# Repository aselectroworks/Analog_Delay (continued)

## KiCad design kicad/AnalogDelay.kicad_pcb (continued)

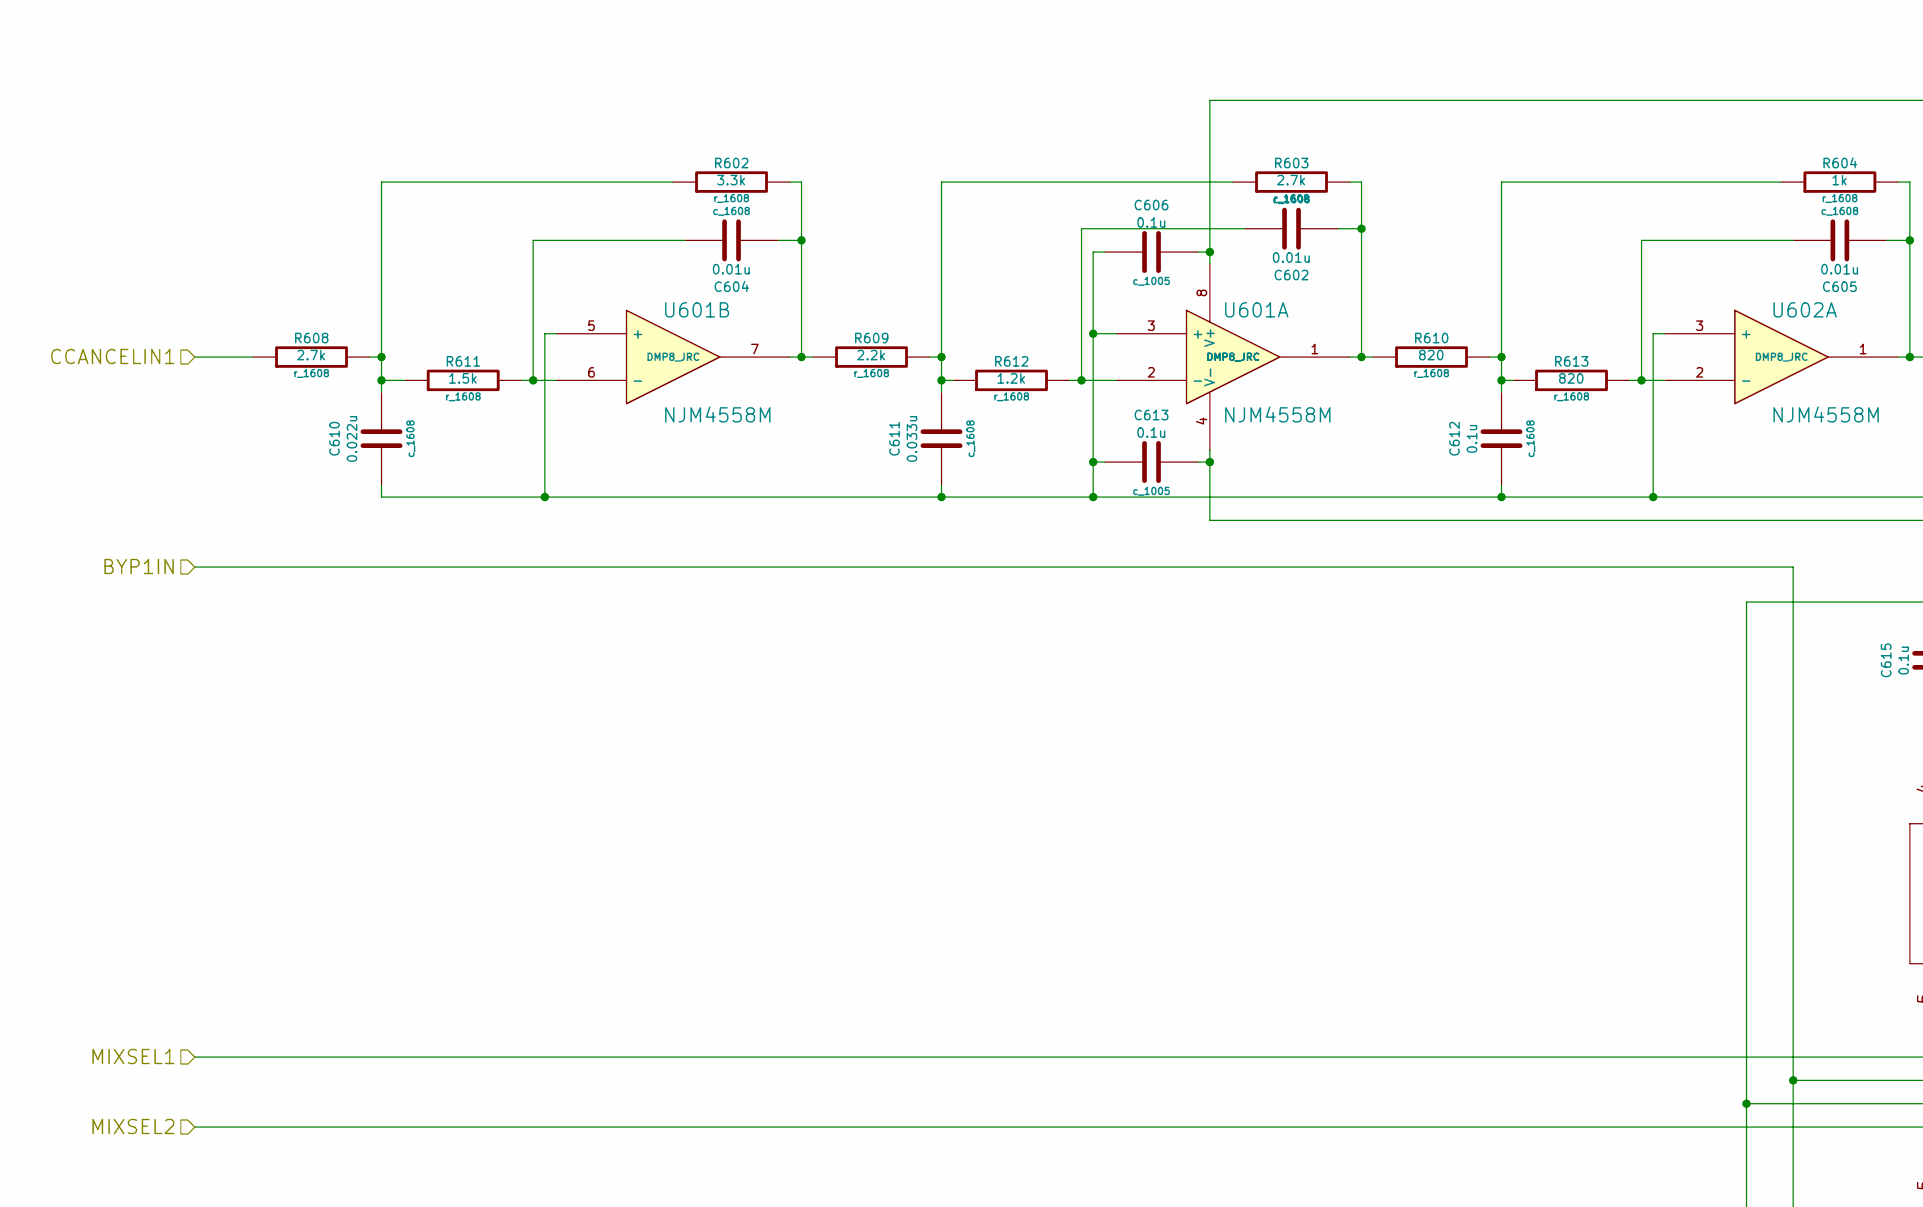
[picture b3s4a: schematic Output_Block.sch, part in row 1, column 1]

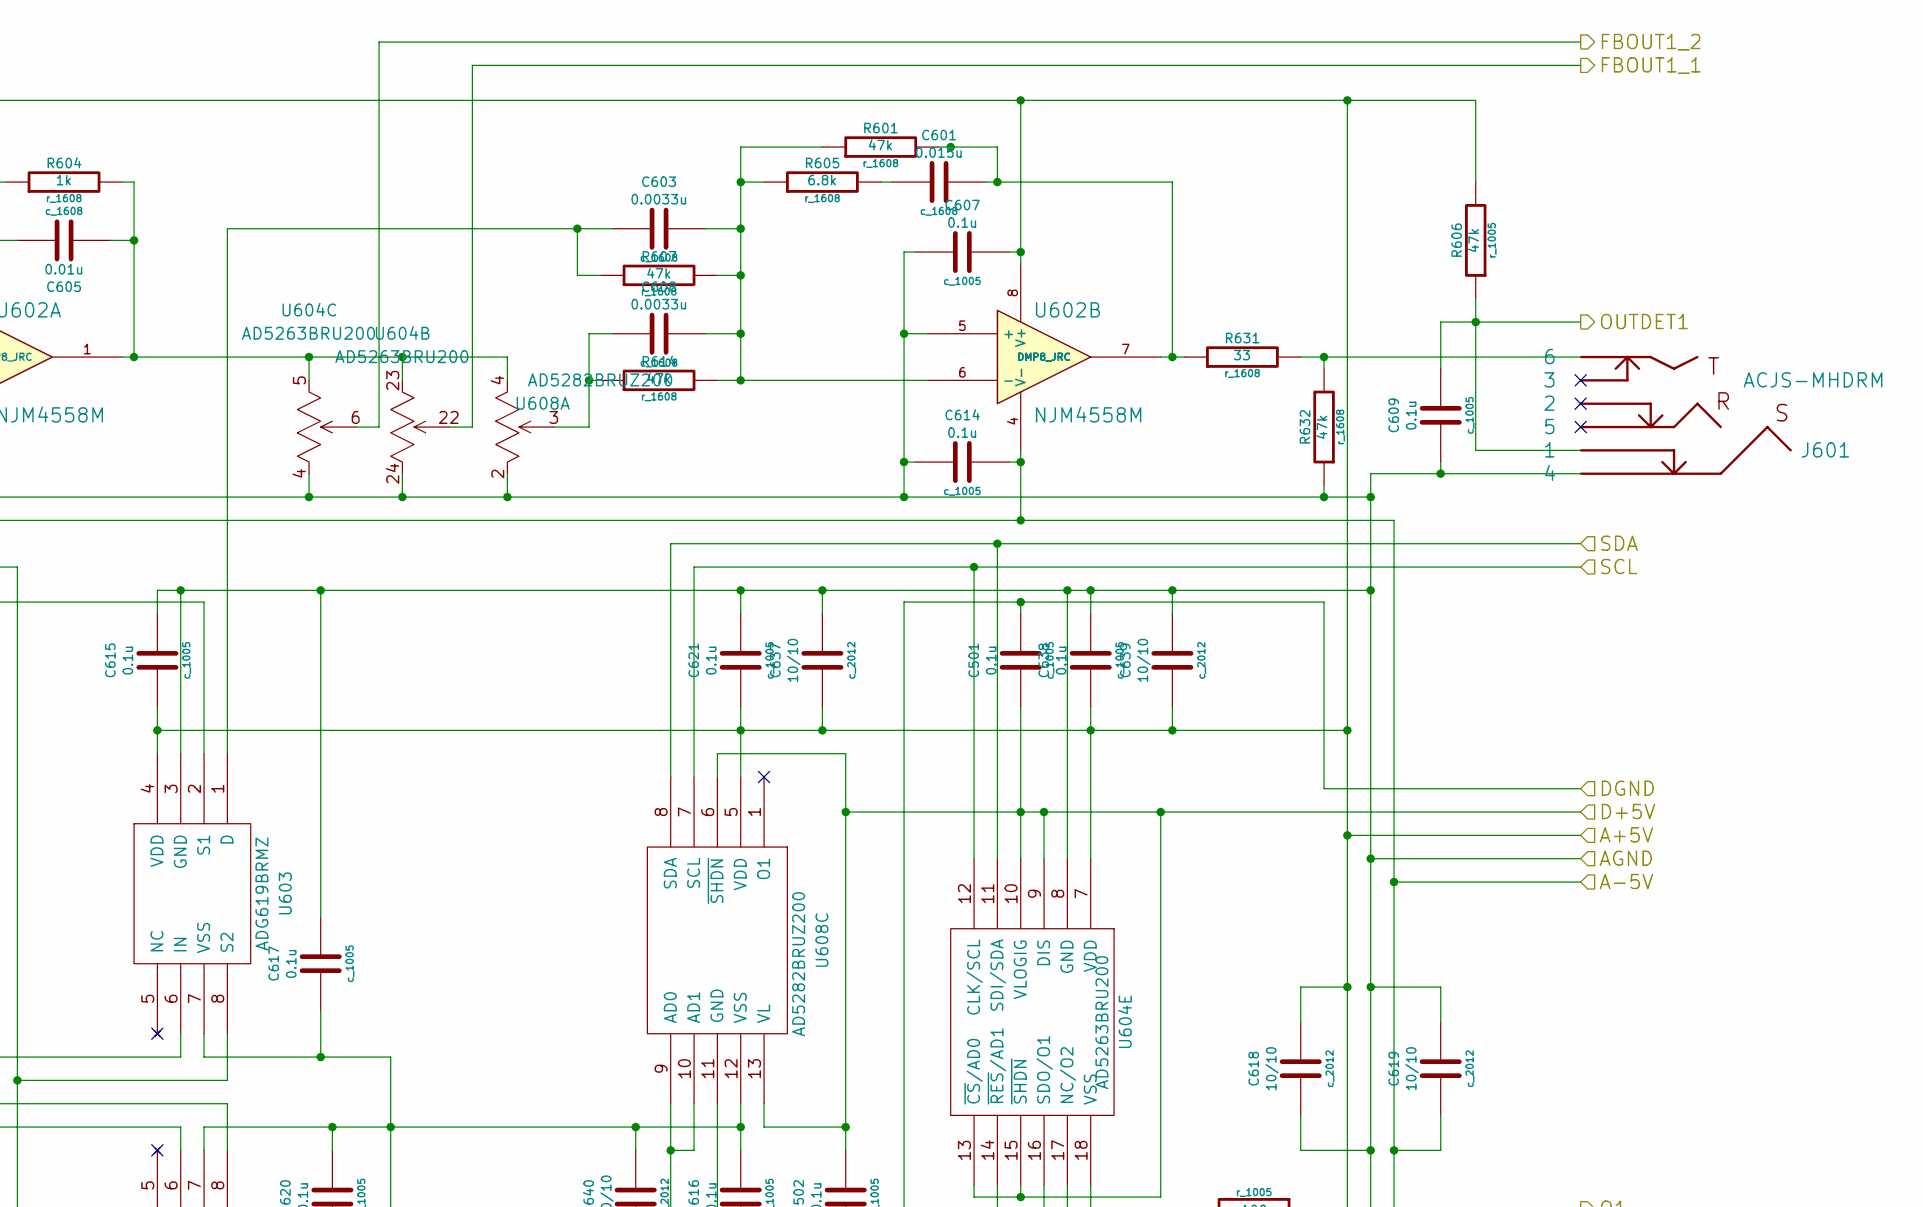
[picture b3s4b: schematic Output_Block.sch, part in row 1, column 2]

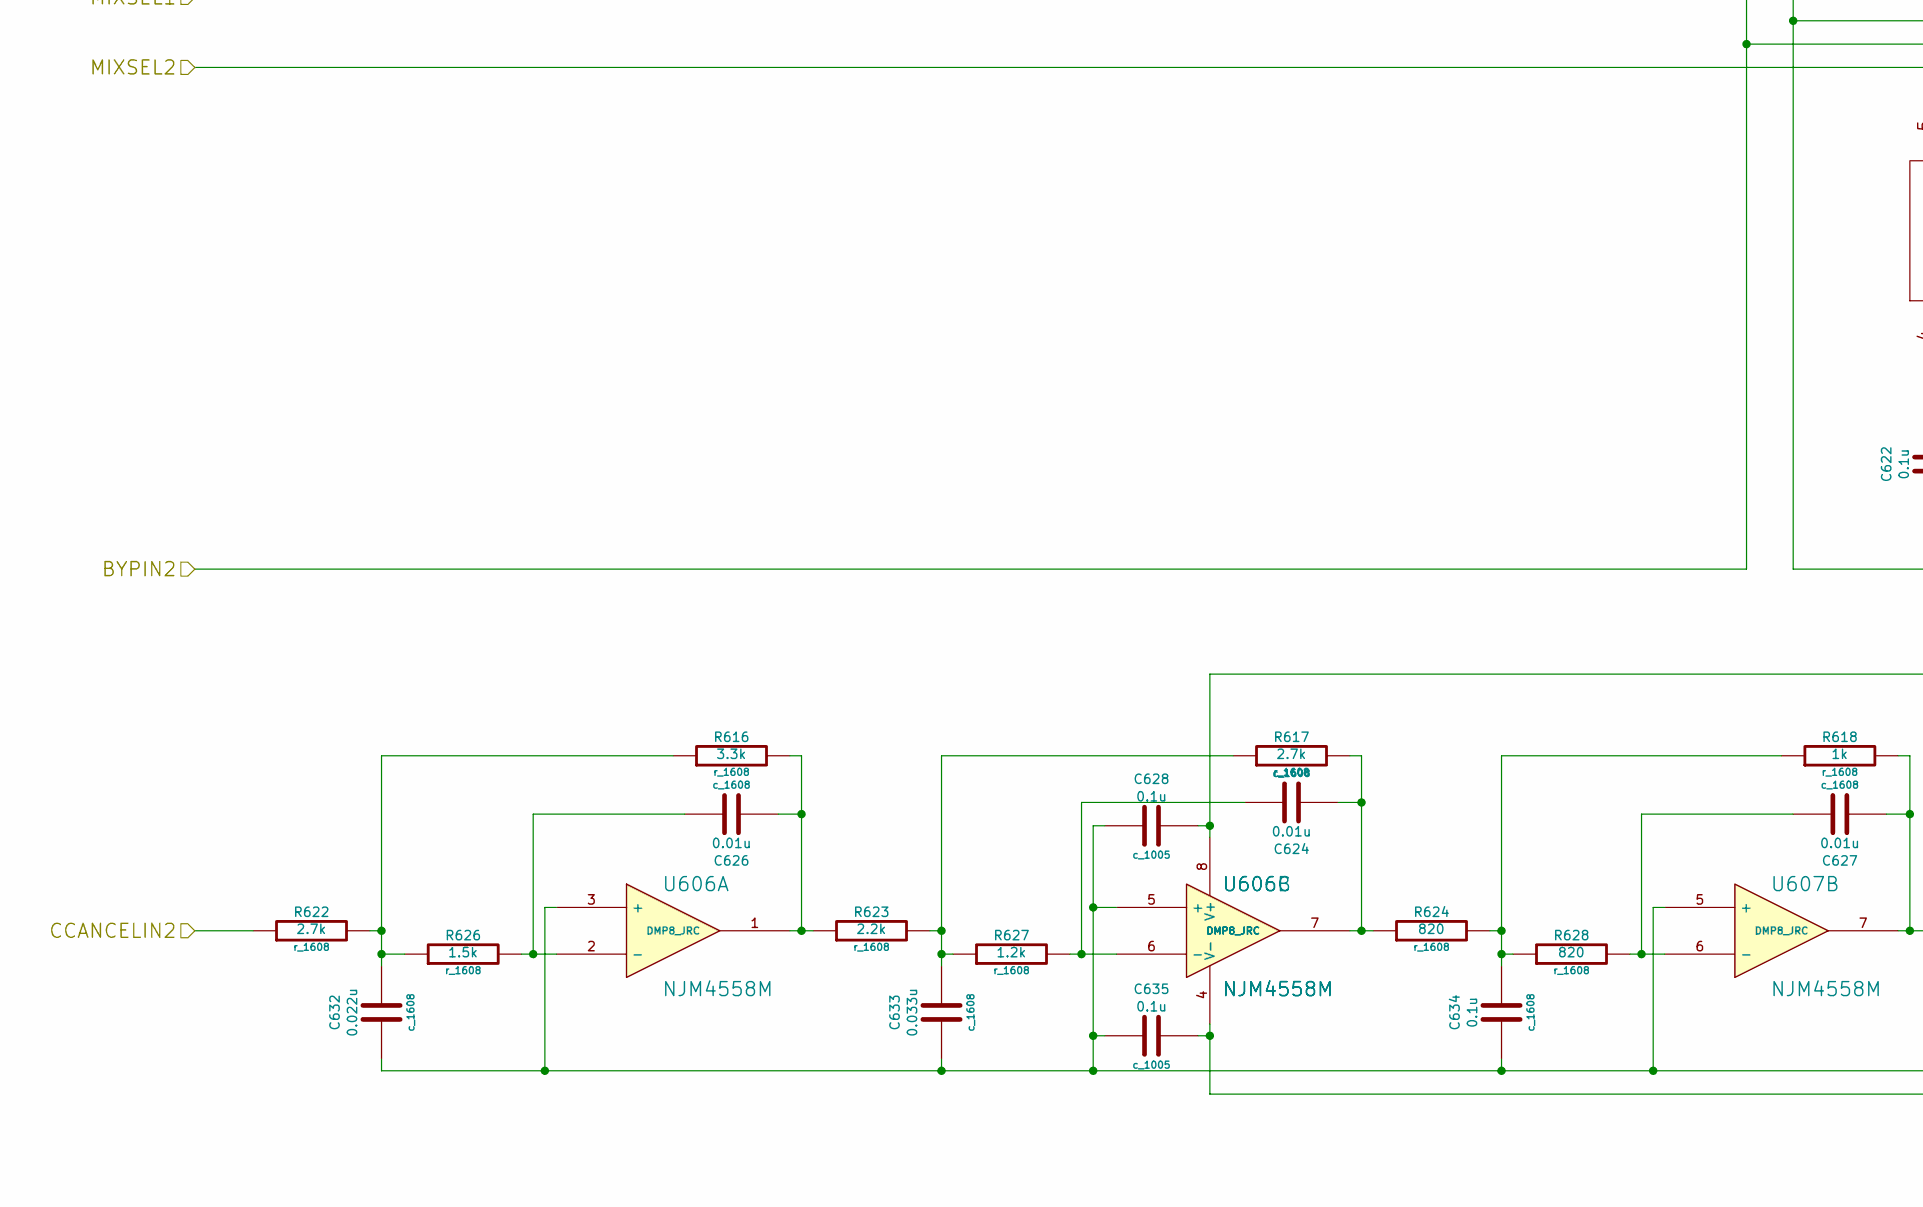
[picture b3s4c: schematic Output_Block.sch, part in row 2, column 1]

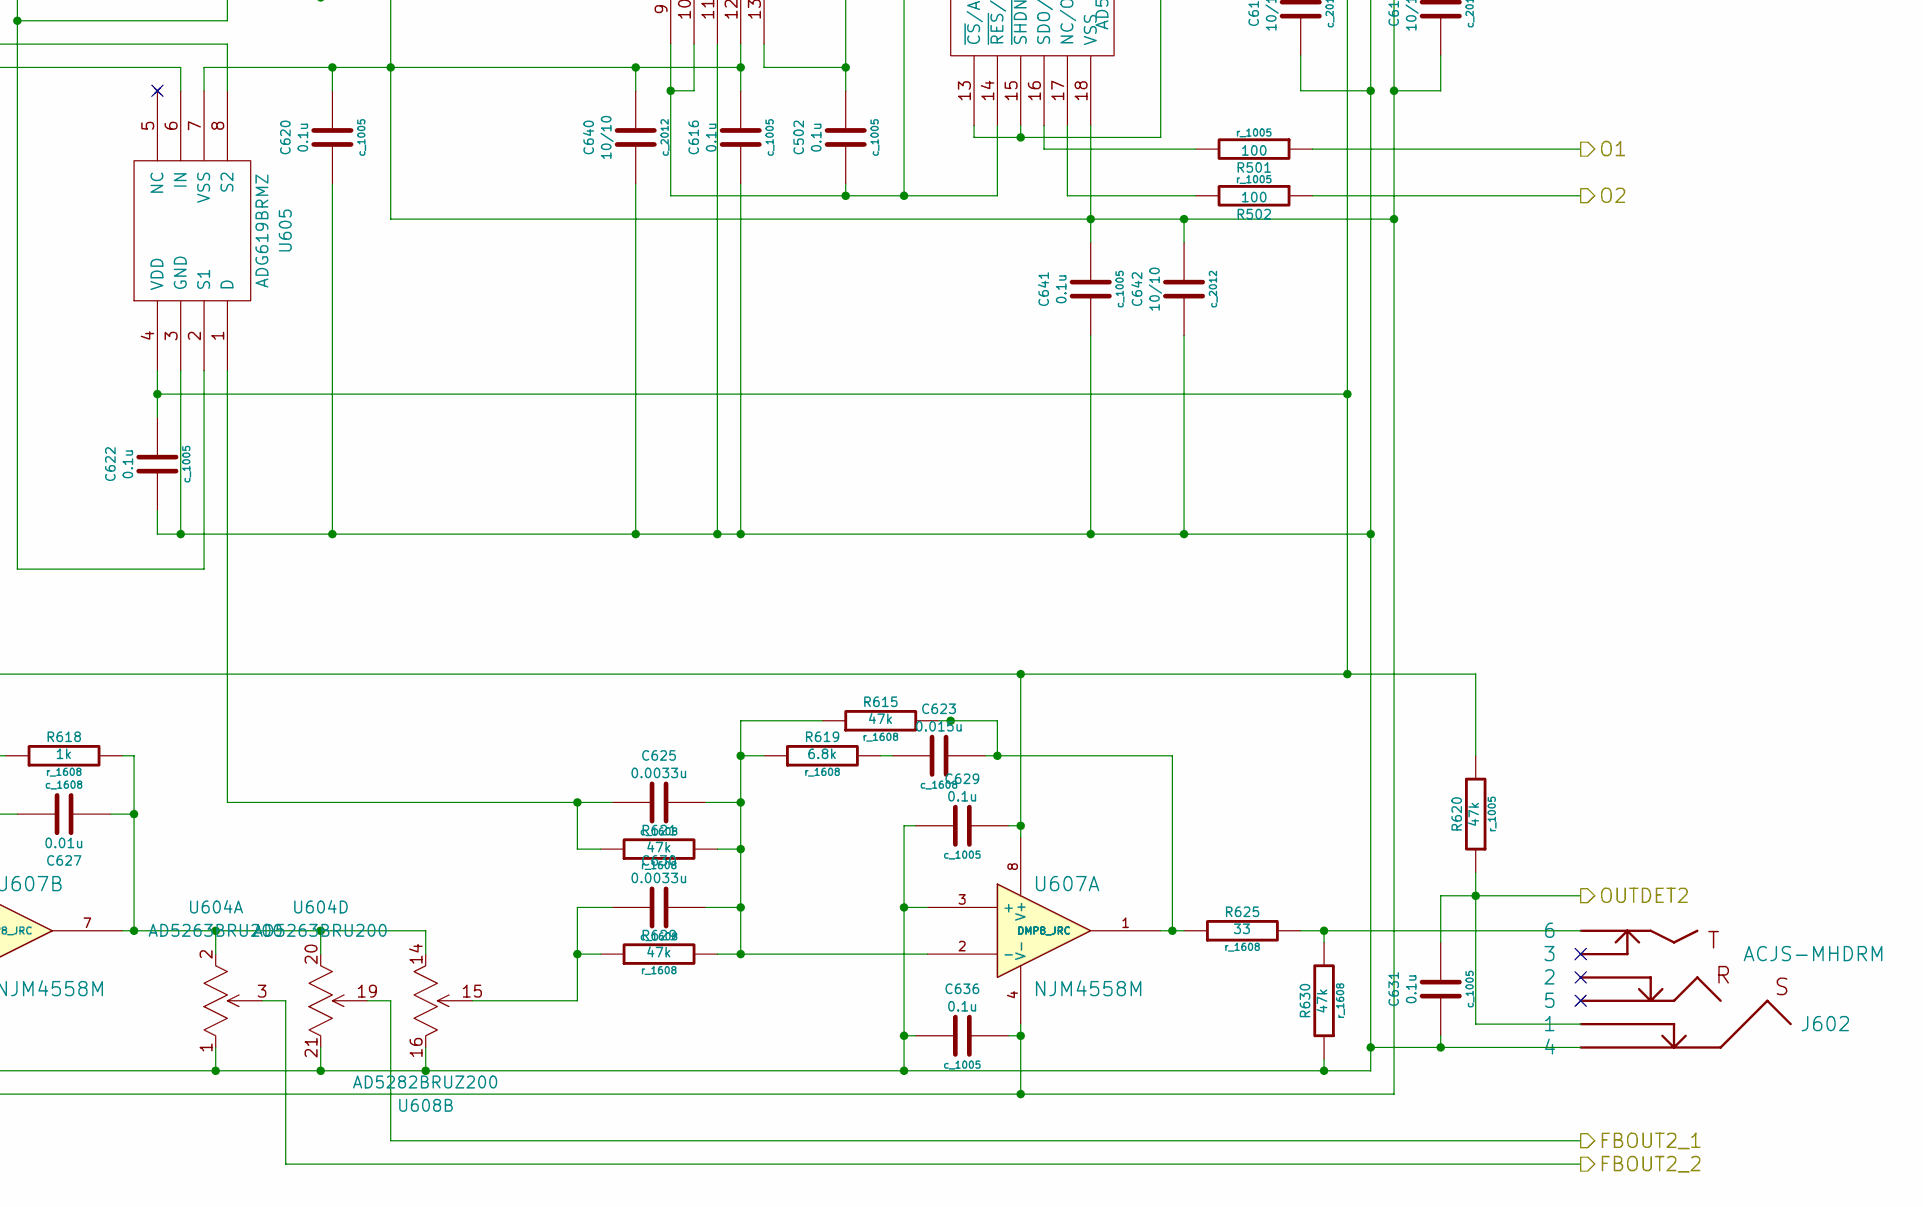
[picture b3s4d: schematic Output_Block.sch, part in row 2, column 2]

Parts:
C501, C502, C606, C607, C609, C613, C614, C615, C616, C617, C620, C621, C622, C628, C629, C631, C635, C636, C638, C641: 0.1u; c_1005
C601, C623: 0.015u; c_1608
C602, C604, C605, C624, C626, C627: 0.01u; c_1608
C603, C608, C625, C630: 0.0033u; c_1608
C610, C632: 0.022u; c_1608
C611, C633: 0.033u; c_1608
C612, C634: 0.1u; c_1608
C618, C619, C637, C639, C640, C642: 10/10; c_2012
J601, J602: ACJS-MHDRM
R501, R502: 100; r_1005
R601, R607, R614, R615, R621, R629, R630, R632: 47k; r_1608
R602, R616: 3.3k; r_1608
R603, R608, R617, R622: 2.7k; r_1608
R604, R618: 1k; r_1608
R605, R619: 6.8k; r_1608
R606, R620: 47k; r_1005
R609, R623: 2.2k; r_1608
R610, R613, R624, R628: 820; r_1608
R611, R626: 1.5k; r_1608
R612, R627: 1.2k; r_1608
R625, R631: 33; r_1608
U601, U602, U606, U607: NJM4558M; DMP8_JRC
U603, U605: ADG619BRMZ; RM-8
U604: AD5263BRU200; RU-24
U608: AD5282BRUZ200; RU-16

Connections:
+5VA: C606.2, C607.2, C615.1, C618.2, C621.1, C622.2, C628.2, C629.2, C637.1, C638.1, C639.1, R606.2, R620.2, U601.8 (V+), U602.8 (V+), U603.4 (VDD), U604.7 (VDD), U605.4 (VDD), U606.8 (V+), U607.8 (V+), U608.5 (VDD); also elsewhere on the board
+5VD: C501.1, C502.2, U604.9 (DIS), U604.10 (VLOGIG), U604.13 (~CS~/AD0), U604.15 (~SHDN), U608.6 (~SHDN), U608.13 (VL); also elsewhere on the board
-5VA: C613.2, C614.2, C616.2, C617.1, C619.1, C620.2, C635.2, C636.2, C640.2, C641.2, C642.2, U601.4 (V-), U602.4 (V-), U603.7 (VSS), U604.18 (VSS), U605.7 (VSS), U606.4 (V-), U607.4 (V-), U608.12 (VSS); also elsewhere on the board
/BBD Block/BBDOUT1: R608.1; also elsewhere on the board
/BBD Block/BBDOUT2: R622.1; also elsewhere on the board
/Clock Cancel Filter/Output Block/BYP1IN: U603.8 (S2), U605.2 (S1); also elsewhere on the board
/Clock Cancel Filter/Output Block/BYPIN2: U603.2 (S1), U605.8 (S2); also elsewhere on the board
/Clock Cancel Filter/Output Block/MIXSEL1: R501.1, U603.6 (IN)
/Clock Cancel Filter/Output Block/MIXSEL2: R502.1, U605.6 (IN)
/Clock Cancel Filter/Output Block/OUTDET1: C609.2, J601.1, R606.1; also elsewhere on the board
/Clock Cancel Filter/Output Block/OUTDET2: C631.2, J602.1, R620.1; also elsewhere on the board
/Clock Cancel Filter/Output Block/SCL: U604.12 (CLK/SCL), U608.7 (SCL); also elsewhere on the board
/Clock Cancel Filter/Output Block/SDA: U604.11 (SDI/SDA), U608.8 (SDA); also elsewhere on the board
/Input/Anti Alias Filter Block/FBIN1_1: U604.22 (W2); also elsewhere on the board
/Input/Anti Alias Filter Block/FBIN1_2: U604.6 (W3); also elsewhere on the board
/Input/Anti Alias Filter Block/FBIN2_1: U604.19 (W4); also elsewhere on the board
/Input/Anti Alias Filter Block/FBIN2_2: U604.3 (W1); also elsewhere on the board
AGND: C606.1, C607.1, C609.1, C610.1, C611.1, C612.1, C613.1, C614.1, C615.2, C616.1, C617.2, C618.1, C619.2, C620.1, C621.2, C622.1, C628.1, C629.1, C631.1, C632.1, C633.1, C634.1, C635.1, C636.1, C637.2, C638.2, C639.2, C640.1, C641.1, C642.1, J601.4, J602.4, R630.1, R632.1, U601.3 (+), U601.5 (+), U602.3 (+), U602.5 (+), U603.3 (GND), U604.1 (B1), U604.4 (B3), U604.8 (GND), U604.21 (B4), U604.24 (B2), U605.3 (GND), U606.3 (+), U606.5 (+), U607.3 (+), U607.5 (+), U608.2 (A1), U608.11 (GND), U608.16 (A1); also elsewhere on the board
DGND: C501.2, C502.1, U604.14 (~RES~/AD1), U608.9 (AD0), U608.10 (AD1); also elsewhere on the board
unnamed: J602.6, R625.2, R630.2
unnamed: C630.1, R629.1, U608.15 (W2)
unnamed: J601.6, R631.2, R632.2
unnamed: C612.2, R604.1, R610.2, R613.1
unnamed: C602.1, R603.2, R610.1, U601.1
unnamed: C602.2, R612.2, U601.2 (-)
unnamed: C608.1, R614.1, U608.3 (W2)
unnamed: C611.2, R603.1, R609.2, R612.1
unnamed: C605.2, R613.2, U602.2 (-)
unnamed: C601.1, R605.2
unnamed: C604.2, R611.2, U601.6 (-)
unnamed: C604.1, R602.2, R609.1, U601.7
unnamed: C610.2, R602.1, R608.2, R611.1
unnamed: C601.2, R601.2, R631.1, U602.7
unnamed: C627.2, R628.2, U607.6 (-)
unnamed: C634.2, R618.1, R624.2, R628.1
unnamed: C624.1, R617.2, R624.1, U606.7
unnamed: C625.1, R621.1, U605.1 (D)
unnamed: C624.2, R627.2, U606.6 (-)
unnamed: C627.1, R618.2, U604.2 (A1), U604.20 (A4), U607.7, U608.14 (B1)
unnamed: C623.2, R615.2, R625.1, U607.1
unnamed: C623.1, R619.2
unnamed: C625.2, C630.2, R615.1, R619.1, R621.2, R629.2, U607.2 (-)
unnamed: C603.1, R607.1, U603.1 (D)
unnamed: C603.2, C608.2, R601.1, R605.1, R607.2, R614.2, U602.6 (-)
unnamed: C633.2, R617.1, R623.2, R627.1
unnamed: C626.1, R616.2, R623.1, U606.1
unnamed: C626.2, R626.2, U606.2 (-)
unnamed: C632.2, R616.1, R622.2, R626.1
unnamed: R501.2, U604.16 (SDO/O1)
unnamed: R502.2, U604.17 (NC/O2)
unnamed: C605.1, R604.2, U602.1, U604.5 (A3), U604.23 (A2), U608.4 (B1)

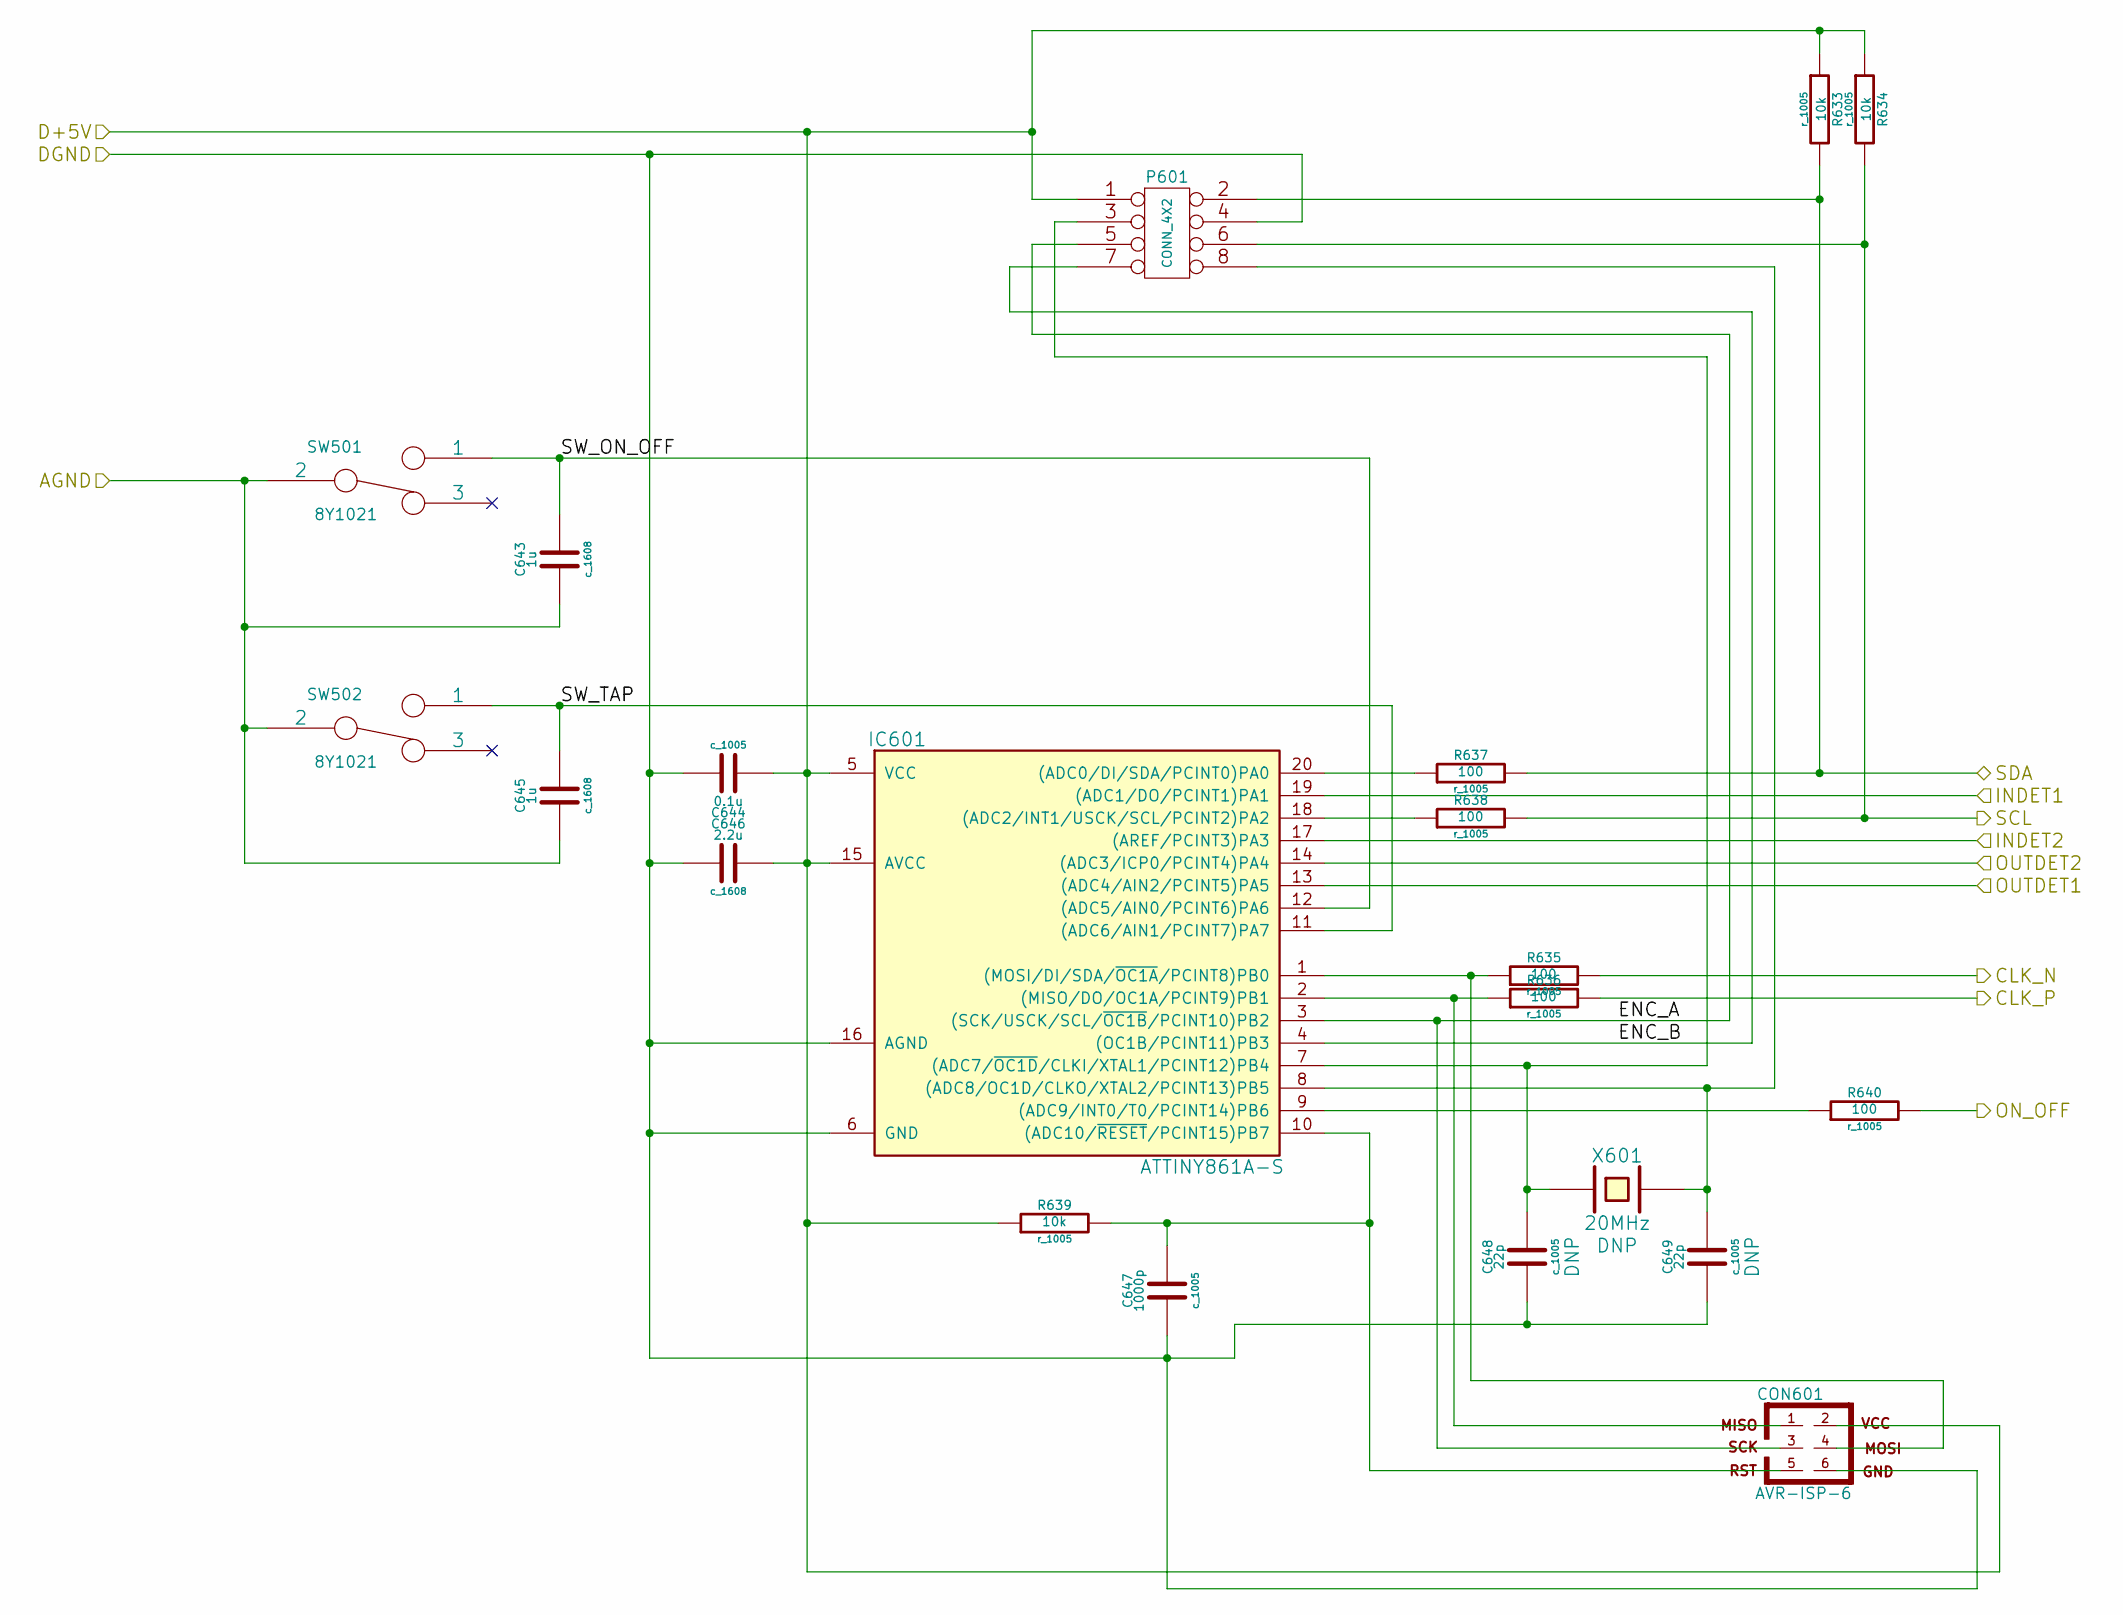
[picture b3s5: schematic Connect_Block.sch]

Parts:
C643, C645: 1u; c_1608
C644: 0.1u; c_1005
C646: 2.2u; c_1608
C647: 1000p; c_1005
C648, C649: 22p; c_1005
CON601: AVR-ISP-6
IC601: ATTINY861A-S; SO20
P601: CONN_4X2
R633, R634, R639: 10k; r_1005
R635, R636, R637, R638, R640: 100; r_1005
SW501, SW502: 8Y1021; 8Y10
X601: 20MHz

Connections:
+5VD: C644.1, C646.2, CON601.2, IC601.5 (VCC), IC601.15 (AVCC), P601.1, R633.1, R634.1, R639.1; also elsewhere on the board
/BBD Block/CLK_N: R635.2; also elsewhere on the board
/BBD Block/CLK_P: R636.2; also elsewhere on the board
/Clock Cancel Filter/Output Block/OUTDET1: IC601.13 ((ADC4/AIN2/PCINT5)PA5); also elsewhere on the board
/Clock Cancel Filter/Output Block/OUTDET2: IC601.14 ((ADC3/ICP0/PCINT4)PA4); also elsewhere on the board
/Clock Cancel Filter/Output Block/SCL: P601.6, R634.2, R638.2; also elsewhere on the board
/Clock Cancel Filter/Output Block/SDA: P601.2, R633.2, R637.2; also elsewhere on the board
/Connect Block/ENC_A: CON601.3, IC601.3 ((SCK/USCK/SCL/~OC1B~/PCINT10)PB2), P601.5
/Connect Block/ENC_B: IC601.4 ((OC1B/PCINT11)PB3), P601.7
/Connect Block/ON_OFF: R640.2; also elsewhere on the board
/Connect Block/SW_ON_OFF: C643.2, IC601.12 ((ADC5/AIN0/PCINT6)PA6), SW501.1
/Connect Block/SW_TAP: C645.2, IC601.11 ((ADC6/AIN1/PCINT7)PA7), SW502.1
/Input/Anti Alias Filter Block/IN1DET: IC601.19 ((ADC1/DO/PCINT1)PA1); also elsewhere on the board
/Input/Anti Alias Filter Block/IN2DET: IC601.17 ((AREF/PCINT3)PA3); also elsewhere on the board
AGND: C643.1, C645.1, SW501.2, SW502.2; also elsewhere on the board
DGND: C644.2, C646.1, C647.1, C648.1, C649.1, CON601.6, IC601.6 (GND), IC601.16 (AGND), P601.4; also elsewhere on the board
unnamed: IC601.18 ((ADC2/INT1/USCK/SCL/PCINT2)PA2), R638.1
unnamed: IC601.20 ((ADC0/DI/SDA/PCINT0)PA0), R637.1
unnamed: C647.2, CON601.5, IC601.10 ((ADC10/~RESET~/PCINT15)PB7), R639.2
unnamed: C649.2, IC601.8 ((ADC8/OC1D/CLKO/XTAL2/PCINT13)PB5), P601.8, X601.2
unnamed: C648.2, IC601.7 ((ADC7/~OC1D~/CLKI/XTAL1/PCINT12)PB4), P601.3, X601.1
unnamed: IC601.9 ((ADC9/INT0/T0/PCINT14)PB6), R640.1
unnamed: CON601.1, IC601.2 ((MISO/DO/OC1A/PCINT9)PB1), R636.1
unnamed: CON601.4, IC601.1 ((MOSI/DI/SDA/~OC1A~/PCINT8)PB0), R635.1
